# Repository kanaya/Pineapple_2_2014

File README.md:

Pineapple_2_2014
================

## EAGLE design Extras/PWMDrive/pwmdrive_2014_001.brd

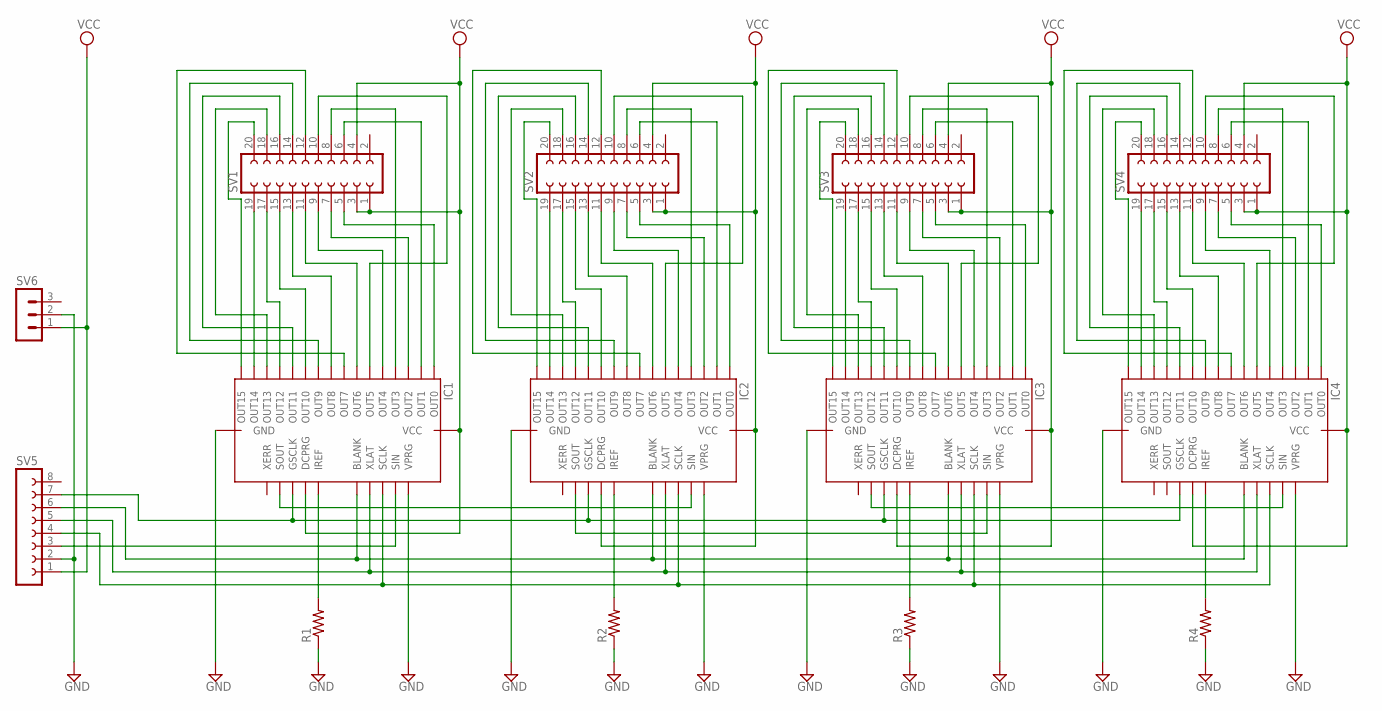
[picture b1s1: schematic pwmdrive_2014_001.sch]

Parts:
IC1, IC2, IC3, IC4: IC-PACKAGE_DIL28; IC-PACKAGE_DIL28-6
R1, R2, R3, R4: R-US_0204/7; 0204/7
SV1, SV2, SV3, SV4: FE10-2
SV5: FE08-1; FE08
SV6: MA03-1

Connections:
GND: IC1.22 (GND), IC1.27 (VPRG), IC2.22 (GND), IC2.27 (VPRG), IC3.22 (GND), IC3.27 (VPRG), IC4.22 (GND), IC4.27 (VPRG), R1.1, R2.1, R3.1, R4.1, SV5.2, SV6.2
unnamed: IC1.17 (SOUT), IC2.26 (SIN)
unnamed: IC2.17 (SOUT), IC3.26 (SIN)
unnamed: IC3.17 (SOUT), IC4.26 (SIN)
unnamed: IC1.24 (XLAT), IC2.24 (XLAT), IC3.24 (XLAT), IC4.24 (XLAT), SV5.5
unnamed: IC1.23 (BLANK), IC2.23 (BLANK), IC3.23 (BLANK), IC4.23 (BLANK), SV5.6
unnamed: IC1.25 (SCLK), IC2.25 (SCLK), IC3.25 (SCLK), IC4.25 (SCLK), SV5.4
unnamed: IC1.18 (GSCLK), IC2.18 (GSCLK), IC3.18 (GSCLK), IC4.18 (GSCLK), SV5.7
unnamed: IC1.20 (IREF), R1.2
unnamed: IC2.20 (IREF), R2.2
unnamed: IC3.20 (IREF), R3.2
unnamed: IC4.20 (IREF), R4.2
unnamed: IC1.26 (SIN), SV5.3
unnamed: IC1.14 (OUT14), SV1.19
unnamed: IC1.12 (OUT12), SV1.17
unnamed: IC1.10 (OUT10), SV1.15
unnamed: IC1.8 (OUT8), SV1.13
unnamed: IC1.6 (OUT6), SV1.11
unnamed: IC1.4 (OUT4), SV1.9
unnamed: IC1.2 (OUT2), SV1.7
unnamed: IC1.28 (OUT0), SV1.5
unnamed: IC1.1 (OUT1), SV1.6
unnamed: IC1.3 (OUT3), SV1.8
unnamed: IC1.15 (OUT15), SV1.20
unnamed: IC1.13 (OUT13), SV1.18
unnamed: IC1.11 (OUT11), SV1.16
unnamed: IC1.9 (OUT9), SV1.14
unnamed: IC1.7 (OUT7), SV1.12
unnamed: IC2.14 (OUT14), SV2.19
unnamed: IC2.28 (OUT0), SV2.5
unnamed: IC2.2 (OUT2), SV2.7
unnamed: IC2.4 (OUT4), SV2.9
unnamed: IC2.6 (OUT6), SV2.11
unnamed: IC2.8 (OUT8), SV2.13
unnamed: IC2.10 (OUT10), SV2.15
unnamed: IC2.12 (OUT12), SV2.17
unnamed: IC2.1 (OUT1), SV2.6
unnamed: IC2.3 (OUT3), SV2.8
unnamed: IC2.5 (OUT5), SV2.10
unnamed: IC2.15 (OUT15), SV2.20
unnamed: IC2.13 (OUT13), SV2.18
unnamed: IC2.11 (OUT11), SV2.16
unnamed: IC2.9 (OUT9), SV2.14
unnamed: IC2.7 (OUT7), SV2.12
unnamed: IC3.14 (OUT14), SV3.19
unnamed: IC3.28 (OUT0), SV3.5
unnamed: IC3.2 (OUT2), SV3.7
unnamed: IC3.4 (OUT4), SV3.9
unnamed: IC3.6 (OUT6), SV3.11
unnamed: IC3.8 (OUT8), SV3.13
unnamed: IC3.10 (OUT10), SV3.15
unnamed: IC3.12 (OUT12), SV3.17
unnamed: IC3.1 (OUT1), SV3.6
unnamed: IC3.3 (OUT3), SV3.8
unnamed: IC3.5 (OUT5), SV3.10
unnamed: IC3.7 (OUT7), SV3.12
unnamed: IC3.15 (OUT15), SV3.20
unnamed: IC3.13 (OUT13), SV3.18
unnamed: IC3.11 (OUT11), SV3.16
unnamed: IC3.9 (OUT9), SV3.14
unnamed: IC4.14 (OUT14), SV4.19
unnamed: IC4.28 (OUT0), SV4.5
unnamed: IC4.2 (OUT2), SV4.7
unnamed: IC4.4 (OUT4), SV4.9
unnamed: IC4.6 (OUT6), SV4.11
unnamed: IC4.8 (OUT8), SV4.13
unnamed: IC4.10 (OUT10), SV4.15
unnamed: IC4.12 (OUT12), SV4.17
unnamed: IC4.15 (OUT15), SV4.20
unnamed: IC4.13 (OUT13), SV4.18
unnamed: IC4.11 (OUT11), SV4.16
unnamed: IC4.9 (OUT9), SV4.14
unnamed: IC4.7 (OUT7), SV4.12
unnamed: IC4.1 (OUT1), SV4.6
unnamed: IC4.3 (OUT3), SV4.8
unnamed: IC4.5 (OUT5), SV4.10
unnamed: IC1.5 (OUT5), SV1.10
VCC: IC1.19 (DCPRG), IC1.21 (VCC), IC2.19 (DCPRG), IC2.21 (VCC), IC3.19 (DCPRG), IC3.21 (VCC), IC4.19 (DCPRG), IC4.21 (VCC), SV1.1, SV1.3, SV1.4, SV2.1, SV2.3, SV2.4, SV3.1, SV3.3, SV3.4, SV4.1, SV4.3, SV4.4, SV5.1, SV6.1

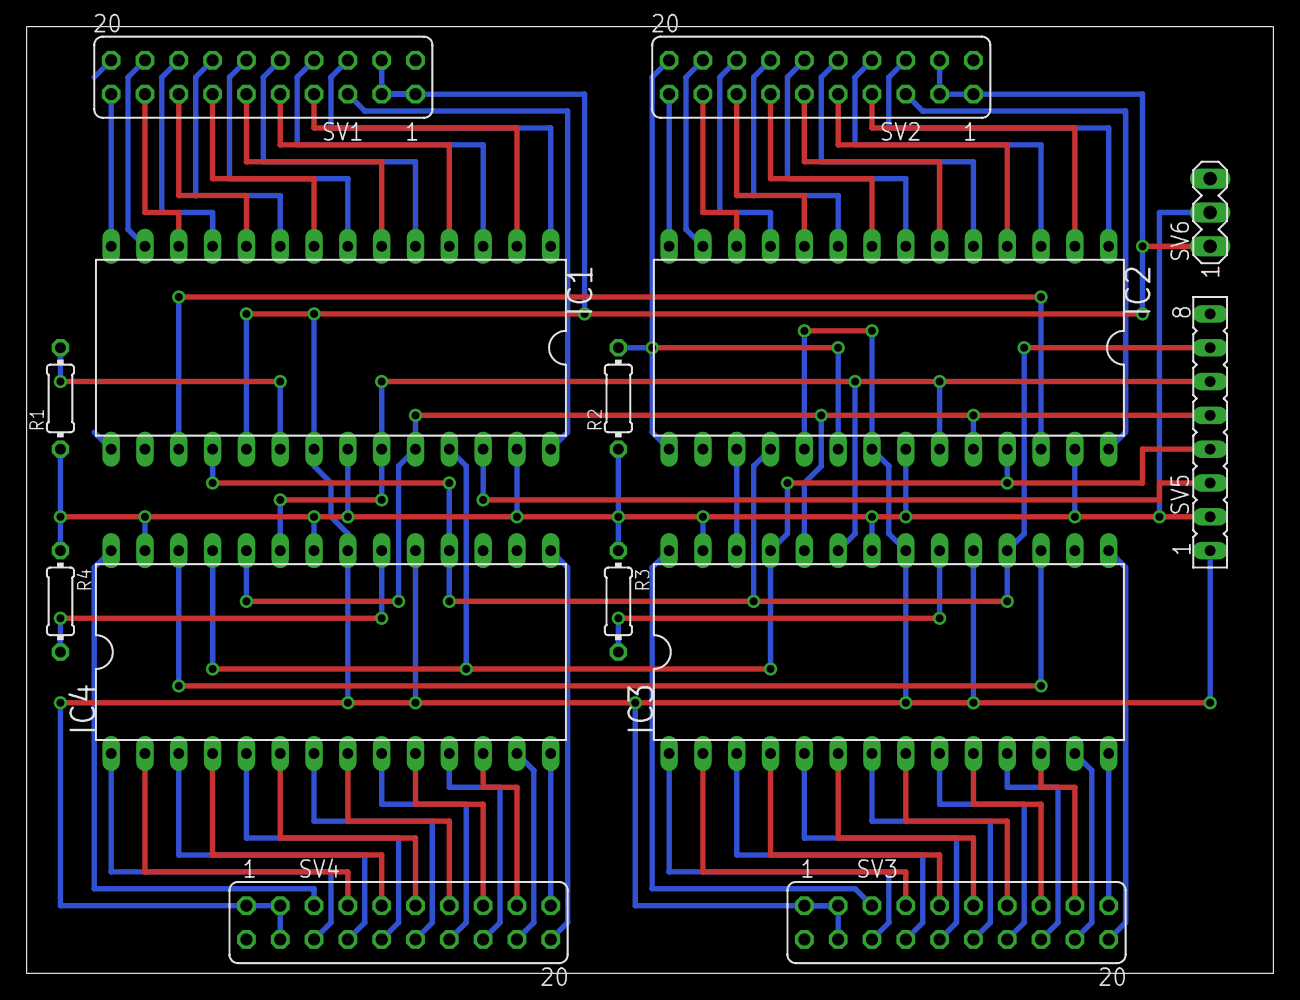
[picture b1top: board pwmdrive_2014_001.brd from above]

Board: 2 copper layers, 93.7 x 71.1 mm, 14 parts (0 on the bottom side), 78 nets.

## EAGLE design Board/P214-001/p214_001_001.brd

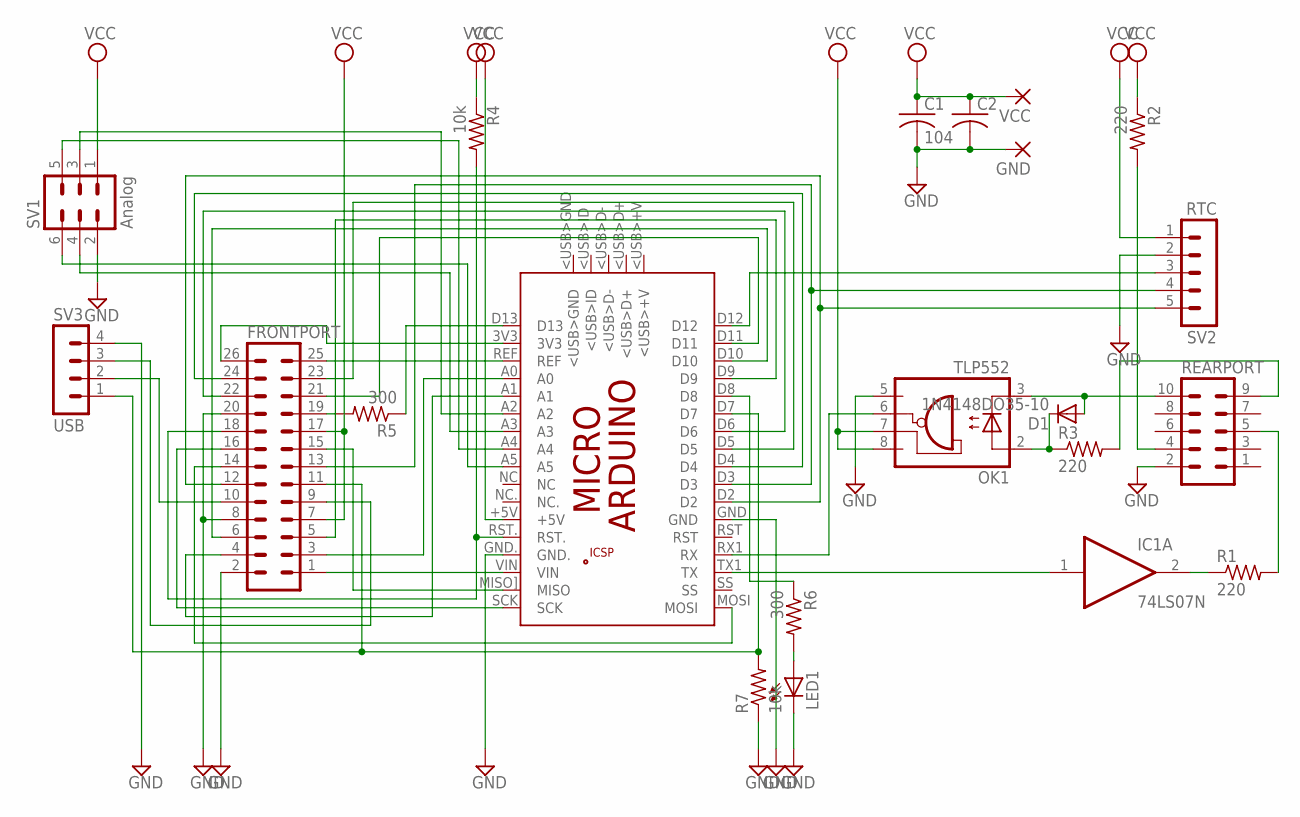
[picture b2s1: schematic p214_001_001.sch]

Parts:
C1: 104; C025-025X050
C2: C-US050-075X075; C050-075X075
D1: 1N4148DO35-10; DO35-10
FRONTPORT: ML26L
GND: 1,6/0,9
IC1: 74LS07N; DIL14
LED1: LED3MM
OK1: TLP552; DIL08
PCB1: ARDUINO_MICRO
R1, R2, R3: 220; 0204/7
R4, R7: 10k; 0204/7
R5, R6: 300; 0204/7
REARPORT: ML10L
SV1: Analog; MA03-2
SV2: RTC; MA05-1
SV3: USB; MA04-1
VCC: 1,6/0,9

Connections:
GND: C1.2, C2.2, FRONTPORT.2, FRONTPORT.8, FRONTPORT.20, GND.1, IC1.7 (GND), LED1.K (C), OK1.5 (GND), PCB1.GND, PCB1.GND., R7.1, REARPORT.2, SV1.2, SV2.2, SV3.4
unnamed: IC1.1 (I), PCB1.TX1 (TX)
unnamed: IC1.2 (O), R1.1
unnamed: D1.C, OK1.2 (A), R3.1
unnamed: R2.2, REARPORT.4
unnamed: R1.2, REARPORT.5
unnamed: R3.2, REARPORT.9
unnamed: D1.A, OK1.3 (C), REARPORT.10
unnamed: OK1.6 (VO), PCB1.RX1 (RX)
unnamed: FRONTPORT.3, PCB1.A0
unnamed: FRONTPORT.1, PCB1.VIN
unnamed: FRONTPORT.4, PCB1.A1
unnamed: FRONTPORT.5, PCB1.D9
unnamed: FRONTPORT.6, PCB1.D10
unnamed: FRONTPORT.14, PCB1.MOSI
unnamed: FRONTPORT.15, PCB1.MISO] (MISO)
unnamed: FRONTPORT.16, PCB1.SCK
unnamed: FRONTPORT.12, PCB1.D2, SV2.5
unnamed: FRONTPORT.13, PCB1.D3, SV2.4
unnamed: FRONTPORT.19, R5.2
unnamed: PCB1.D13, R5.1
unnamed: FRONTPORT.25, PCB1.REF
unnamed: FRONTPORT.9, SV3.3
unnamed: FRONTPORT.18, PCB1.RST., R4.2
unnamed: FRONTPORT.11, PCB1.D7, R7.2, SV3.1
unnamed: FRONTPORT.21, PCB1.D11
unnamed: FRONTPORT.22, PCB1.D6
unnamed: FRONTPORT.23, PCB1.D5
unnamed: FRONTPORT.24, PCB1.D4
unnamed: FRONTPORT.26, PCB1.3V3
unnamed: PCB1.A2, SV1.3
unnamed: PCB1.A3, SV1.4
unnamed: PCB1.A4, SV1.5
unnamed: PCB1.A5, SV1.6
unnamed: PCB1.D8, R6.1
unnamed: LED1.A, R6.2
unnamed: PCB1.D12, SV2.3
unnamed: FRONTPORT.10, SV3.2
VCC: C1.1, C2.1, FRONTPORT.7, FRONTPORT.17, IC1.14 (VCC), OK1.7 (VE), OK1.8 (VCC), PCB1.+5V, R2.1, R4.1, SV1.1, SV2.1, VCC.1

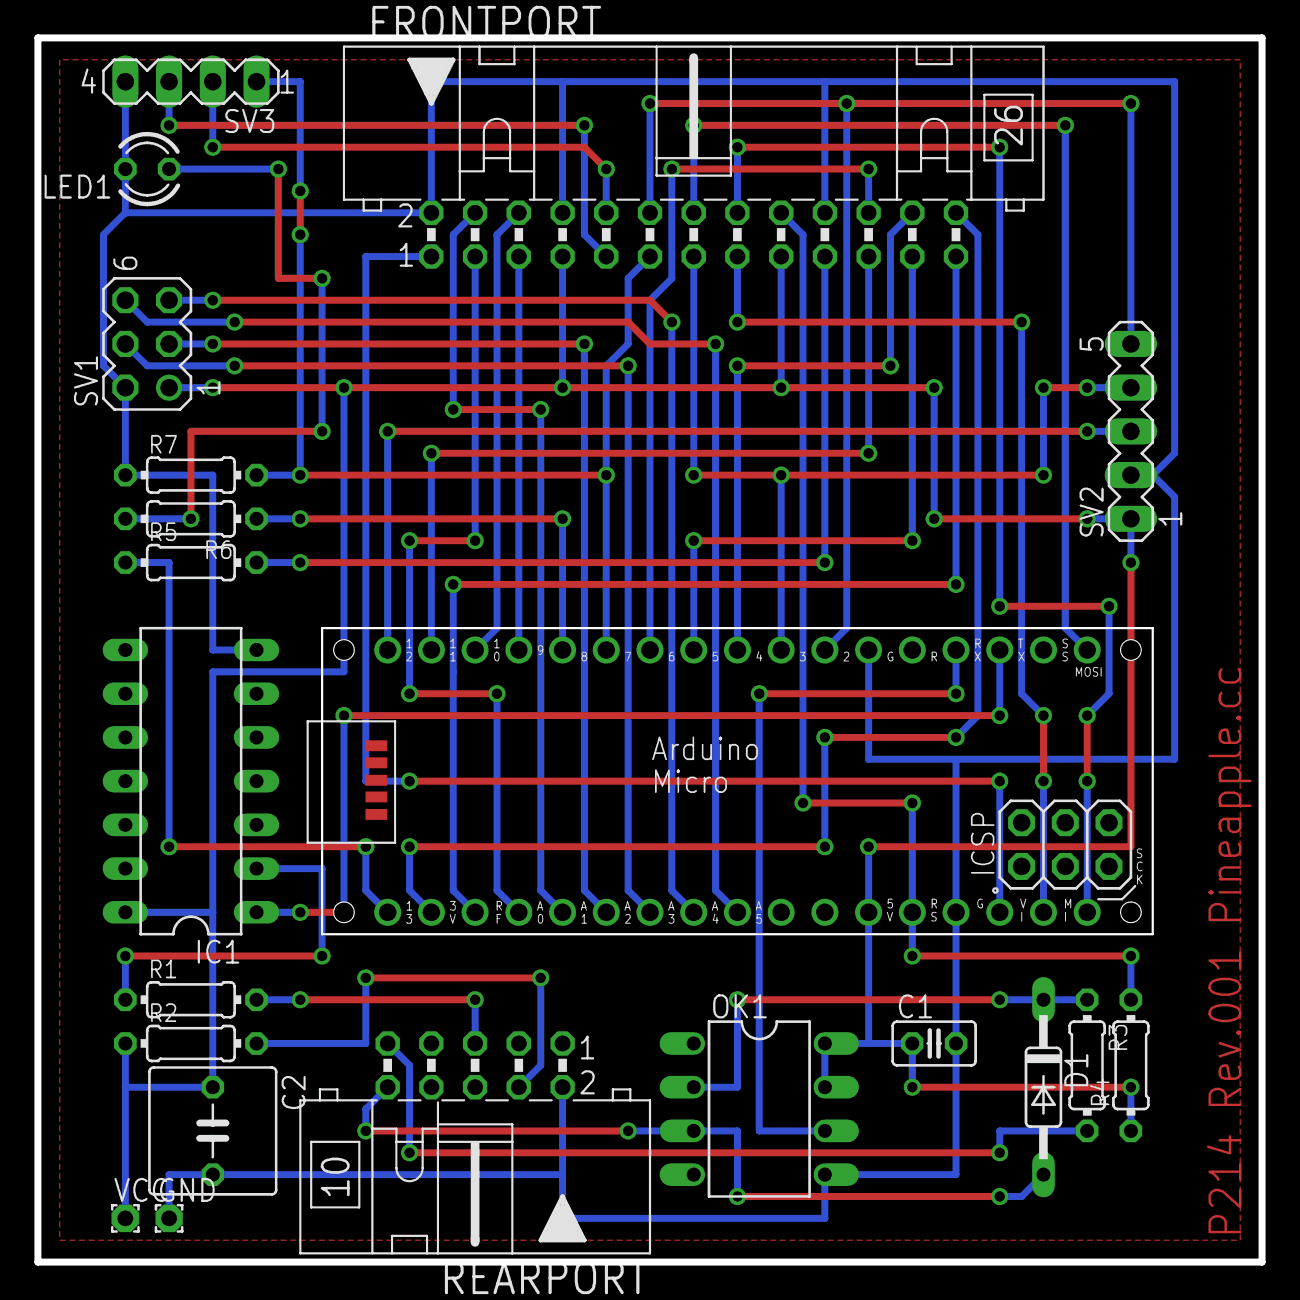
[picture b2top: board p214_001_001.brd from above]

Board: 2 copper layers, 71.1 x 71.1 mm, 21 parts (0 on the bottom side), 39 nets.

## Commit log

2014-01-19 Panels.
2014-02-13 new board design.
2014-02-13 removed old files.
2014-02-15 new design.
2014-02-16 i2c socket
2014-02-26 added Extras.
